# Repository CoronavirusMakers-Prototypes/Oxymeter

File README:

Repositorio del proyecto Oxymeter de Coronavirus Makers

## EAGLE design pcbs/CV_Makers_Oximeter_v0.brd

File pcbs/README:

Fuentes de las PCBs, BOMs, etc.

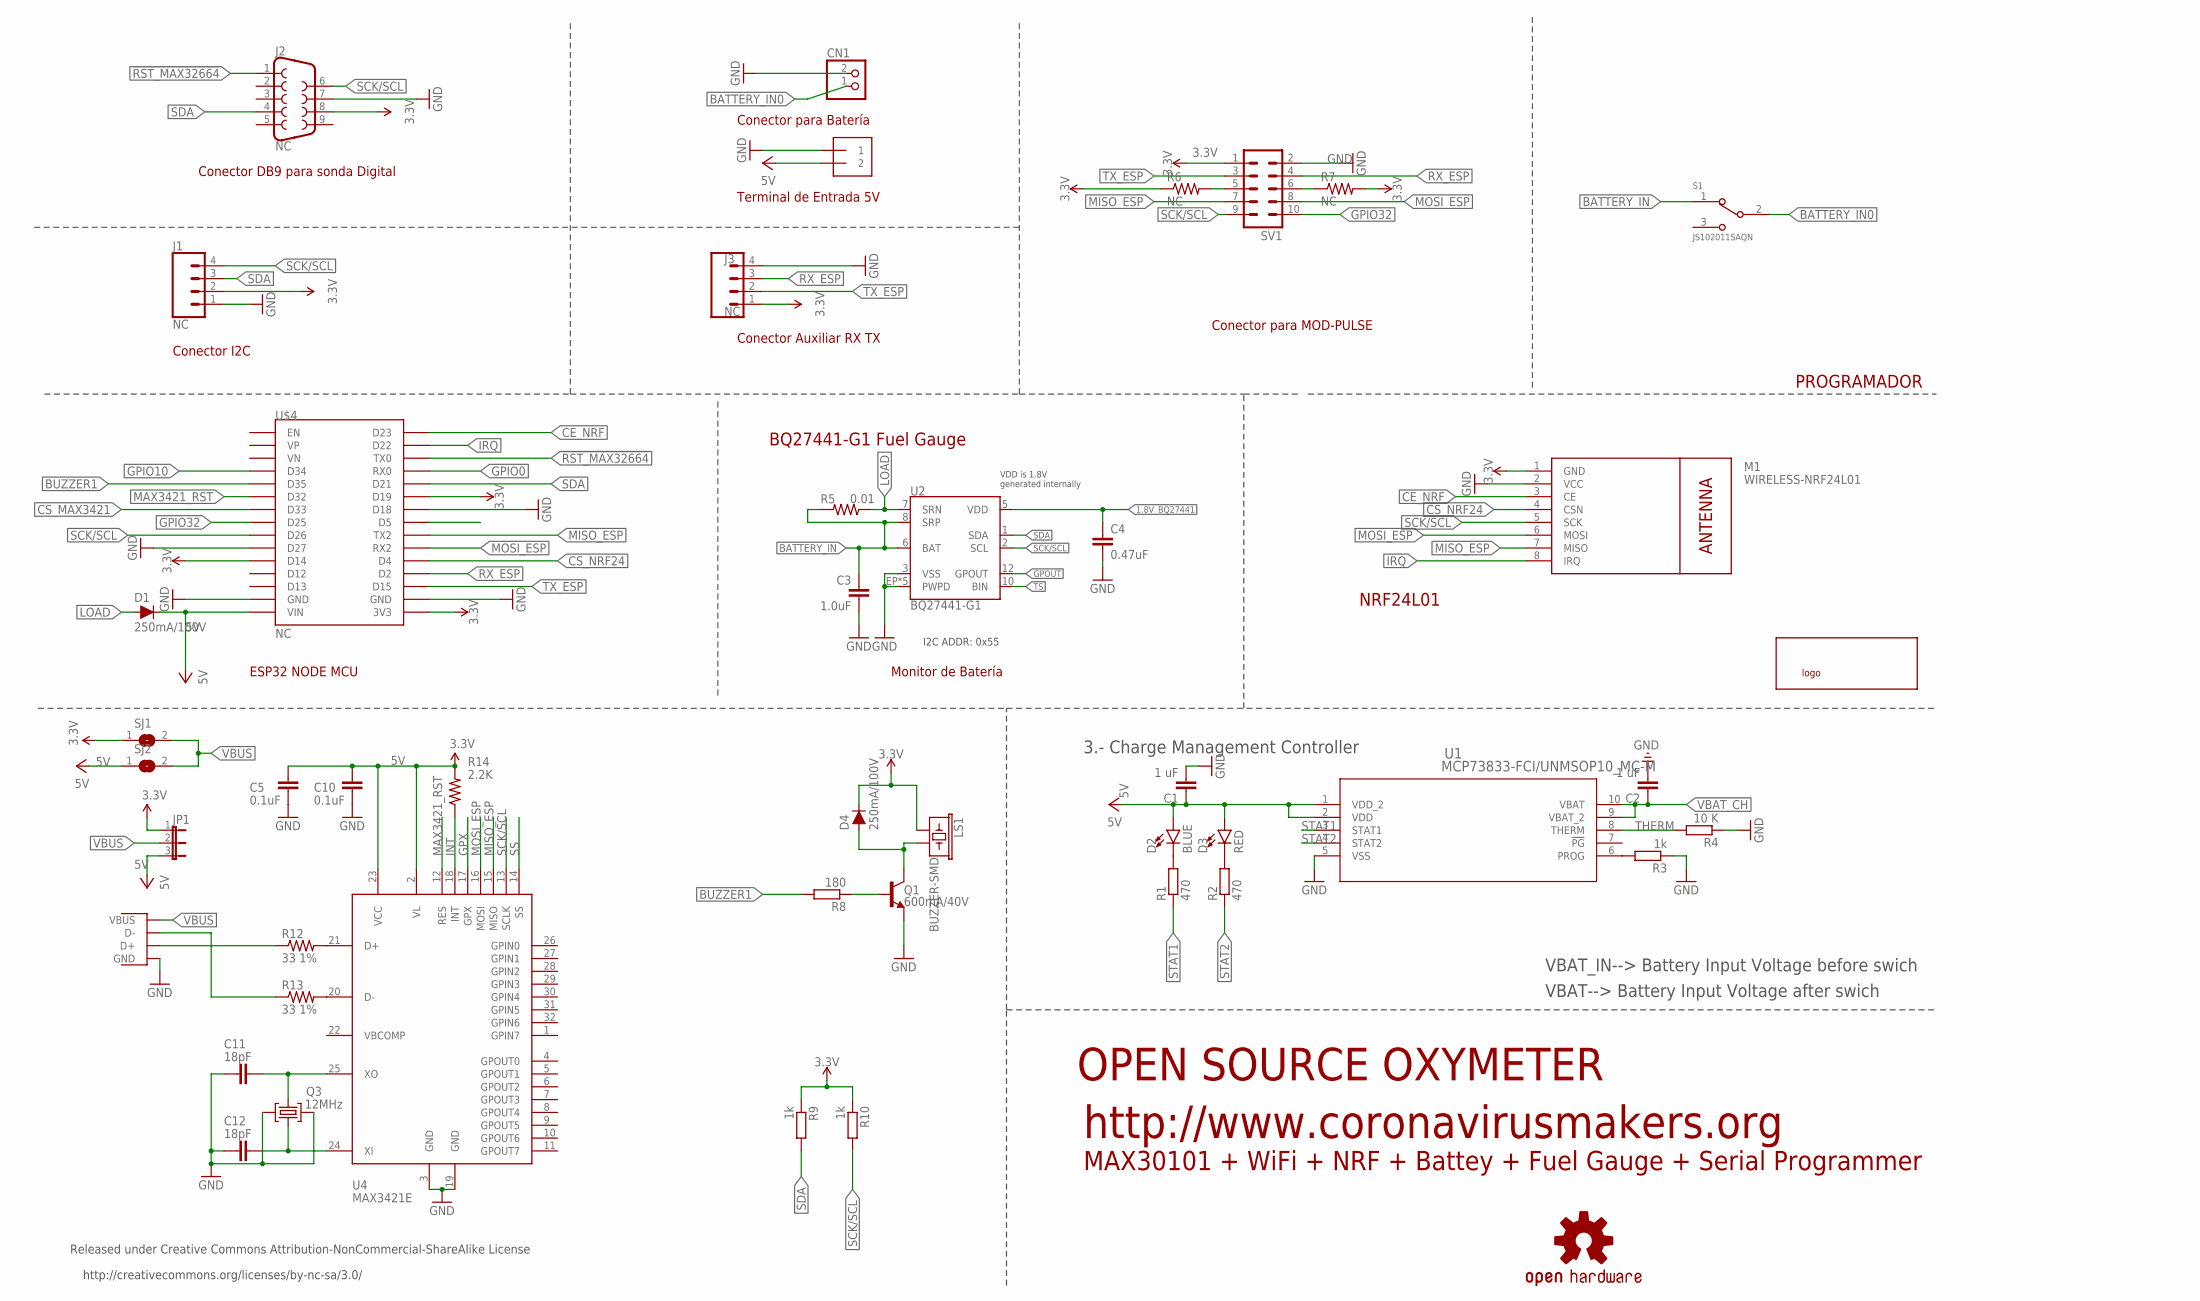
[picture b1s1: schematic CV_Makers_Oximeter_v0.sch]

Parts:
C1, C2: 1 uF; C0603
C3: 1.0uF; 0603-CAP
C4: 0.47uF; 0603-CAP
C5, C10: 0.1uF; 0603
C11, C12: 18pF; 0603
CN1: JST_2PIN-THM-RA; JST-PH-2-THM-RA
D1, D4: 250mA/100V; SOD-323
D2: BLUE; LED-0603
D3: RED; LED-0603
J1, J3: NC; 1X04
J2: NC; DB9
J4: NC; 1X2-3.5MM
JP1: JP2E; JP2
LOGO1: OSHW-LOGOL-COPPER; OSHW-LOGO-L_COPPER
LS1: BUZZER-SMD; BUZZER-CCV
M1: WIRELESS-NRF24L01
Q1: 600mA/40V; SOT23-3
Q3: 12MHz; CRYSTAL-SMD-5X3
R1, R2: 470; R0603
R3, R9, R10: 1k; R0603
R4: 10 K; R0603
R5: 0.01; 1206
R6, R7: NC; R0603
R8: 180; R0603
R12, R13: 33 1%; 0603
R14: 2.2K; 0603
S1: JS102011SAQN; SW_JS102011SAQN
SJ1, SJ2: SJ
SV1: ML10
U1: MCP73833-FCI/UNMSOP10_MC-M; MSOP10_MC-M
U2: BQ27441-G1; PDSO-N12
U4: MAX3421E; TQFP32_8MIL
U$2: LOGOEU; LOGO2
U$4: NC; ESP32_DEVKIT
X2: USB-A-H

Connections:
1.8V_BQ27441: C4.1, U2.5 (VDD)
3.3V: D4.C, J1.2, J2.8, J3.1, JP1.1, LS1.+ (1), M1.1 (GND), R6.1, R7.2, R9.1, R10.1, SJ1.1, SV1.1, U$4.D14, U$4.D19
5V: C1.1, C5.1, C10.1, D1.C, D2.A, D3.A, J4.2, JP1.3, R14.2, SJ2.1, U1.1 (VDD_2), U1.2 (VDD), U4.2 (VL), U4.23 (VCC), U$4.VIN
!RST_MAX32664: J2.1, U$4.TX0
BATTERY_IN: C3.1, R5.2, S1.1, U2.6 (BAT), U2.8 (SRP)
BATTERY_IN0: CN1.1 (2), S1.2
BUZZER1: R8.2, U$4.D35
CE_NRF: M1.3 (CE), U$4.D23
CS_MAX3421: U$4.D33
CS_NRF24: M1.4 (CSN), U$4.D4
GND: C1.2, C2.2, C3.2, C4.2, C5.2, C10.2, C11.1, C12.1, CN1.2 (1), J1.1, J2.7, J3.4, J4.1, M1.2 (VCC), Q1.2 (E), Q3.2 (3), Q3.4, R3.1, R4.1, SV1.2, U1.5 (VSS), U2.3 (VSS), U2.EP (PWPD), U2.EP1 (PWPD), U2.EP2 (PWPD), U2.EP3 (PWPD), U2.EP4 (PWPD), U4.3 (GND), U4.19 (GND), U$4.D18, U$4.GND@1 (GND), X2.GND
GPIO0: U$4.RX0
GPIO10: U$4.D34
GPIO32: SV1.10, U$4.D25
GPOUT: U2.12 (GPOUT)
GPX: U4.17 (GPX)
INT: R14.1, U4.18 (INT)
IRQ: M1.8 (IRQ), U$4.D22
LOAD: D1.A, R5.1, U2.7 (SRN)
MAX3421_RST: U4.12 (RES), U$4.D32
MISO_ESP: M1.7 (MISO), SV1.7, U4.15 (MISO), U$4.TX2
MOSI_ESP: M1.6 (MOSI), SV1.8, U4.16 (MOSI), U$4.RX2
unnamed: R6.2, SV1.5
unnamed: R7.1, SV1.6
unnamed: Q1.1 (B), R8.1
unnamed: D4.A, LS1.- (2), Q1.3 (C)
unnamed: R12.2, U4.21 (D+)
unnamed: D3.C, R2.2
unnamed: R13.2, U4.20 (D-)
unnamed: D2.C, R1.2
unnamed: R3.2, U1.6 (PROG)
unnamed: C11.2, Q3.3 (2), U4.25 (XO)
unnamed: C12.2, Q3.1, U4.24 (XI)
unnamed: R12.1, X2.D+
unnamed: R13.1, X2.D-
RX_ESP: J3.3, SV1.4, U$4.D2
SCK/SCL: J1.4, J2.6, M1.5 (SCK), R10.2, SV1.9, U2.2 (SCL), U4.13 (SCLK), U$4.D26
SDA: J1.3, J2.4, R9.2, U2.1 (SDA), U$4.D21
SS: U4.14 (SS)
STAT1: R1.1, U1.3 (STAT1)
STAT2: R2.1, U1.4 (STAT2)
THERM: R4.2, U1.8 (THERM)
TS: U2.10 (BIN)
TX_ESP: J3.2, SV1.3, U$4.D15
VBAT_CH: C2.1, U1.9 (VBAT_2), U1.10 (VBAT)
VBUS: JP1.2, SJ1.2, SJ2.2, X2.VBUS

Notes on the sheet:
BQ27441-G1 Fuel Gauge
VDD is 1.8V generated internally
I2C ADDR: 0x55
VBAT--> Battery Input Voltage after swich
VBAT_IN--> Battery Input Voltage before swich
3.- Charge Management Controller
PROGRAMADOR
http://www.coronavirusmakers.org
OPEN SOURCE OXYMETER
NRF24L01
MAX30101 + WiFi + NRF + Battey + Fuel Gauge + Serial Programmer
Conector DB9 para sonda Digital
Conector I2C
Conector Auxiliar RX TX
Conector para Batería
Terminal de Entrada 5V
ESP32 NODE MCU
Monitor de Batería
Conector para MOD-PULSE
Released under Creative Commons Attribution-NonCommercial-ShareAlike License
http://creativecommons.org/licenses/by-nc-sa/3.0/

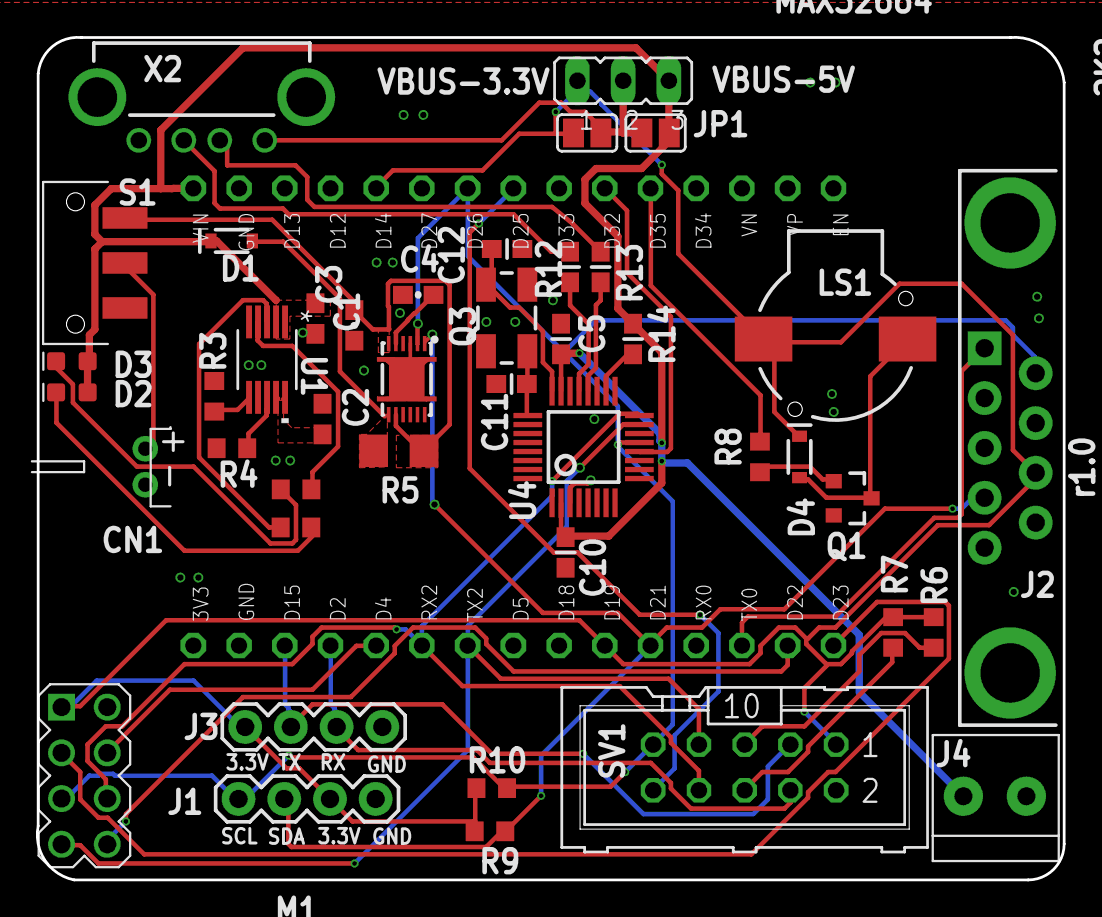
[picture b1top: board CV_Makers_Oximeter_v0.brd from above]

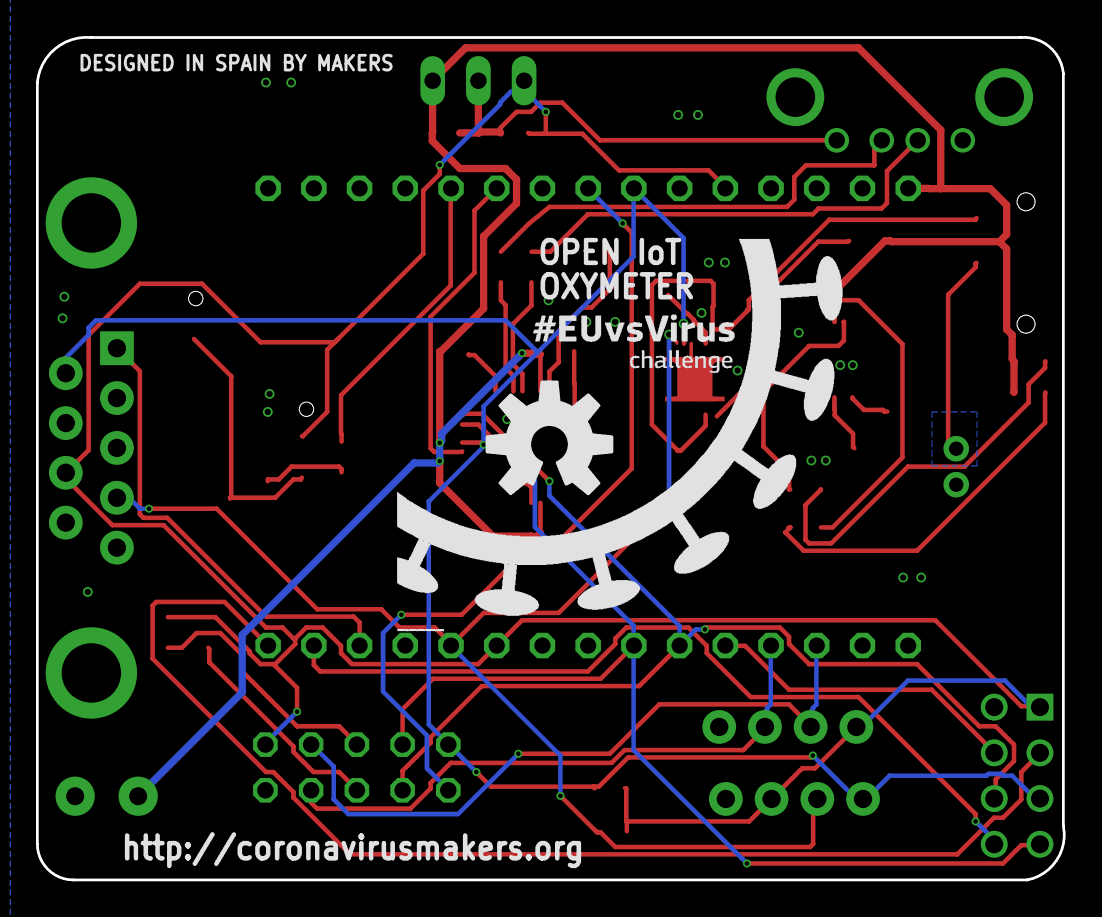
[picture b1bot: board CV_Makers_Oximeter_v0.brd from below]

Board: 2 copper layers, 57.0 x 46.8 mm, 47 parts (2 on the bottom side), 39 nets.

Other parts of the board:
U$1: OSHW-LOGO-L

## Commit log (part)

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2020-03-30 Carga inicial
2020-03-30 first commit, structure, db connections, config
2020-03-30 starting
2020-03-30 websockes rogue
2020-03-30 docker-compose for postgresql dependency
2020-03-31 database design
2020-03-31 adding database from master
2020-03-31 Arquitectura front
2020-04-01 trying to create tables on init via sql file
2020-04-01 Modified User table with jws field
2020-04-01 init database on start if that does not exists, refactoring folder names and adding gitignore to root of repo
2020-04-01 Login / formulario registro / authguard
2020-04-02 basic endpoint for meassurement and sensor, something at README
2020-04-02 first commit to develop
2020-04-02 readme
2020-04-02 simple logging
2020-04-02 removing logs
2020-04-03 better queries handling
2020-04-03 adding checks for request params, more or less ready for duplicate
2020-04-03 improving README
2020-04-03 Componentes por zona
2020-04-03 basic sender and consumer for rabbit, now lets start play around
2020-04-03 adding array payloads for dummy-senders and implementation at the consummer side
2020-04-03 RabbitMQ consumer implementation almost there
2020-04-03 adding rabbitmq for docker composition
2020-04-03 adding credentials to rabbitmq
2020-04-03 Estructura hospital / migas de pan / componente alarmas / servicio utils / servicio alarms / encapsular servicios en global.service
2020-04-04 adding all semicolons since ASI and its excentric behavior and async do things on startup
2020-04-04 changed response to get list for pagination
2020-04-04 updating insomnia export
2020-04-04 implementing rabbitmq sender
2020-04-04 Thanks co 🙏
2020-04-05 Logout a través de globalService / nuevo bed sensor patient service / quito user-asignement.service.ts / clear localStorage on logout
2020-04-05 adding area endpoint and changes at queries to match the new naming
2020-04-05 hospitals working
2020-04-05 build working
2020-04-05 floors working
2020-04-05 room working
2020-04-05 bed working and fix missing id at dummy senders
2020-04-05 roles working
2020-04-05 Servicio paciente
2020-04-05 patient working
2020-04-05 Database modifications
2020-04-05 Sensor data
2020-04-05 updating insomnia file
2020-04-06 new database
2020-04-06 lot of stuff
2020-04-06 Cambio nombre servicio
2020-04-06 Prueba librería gráficas
2020-04-06 Urls librería chart
2020-04-06 added TODOs and descriptions
2020-04-07 Modificación nombres endpoints
2020-04-07 complete and align new endpoints names
2020-04-08 Gráficas
2020-04-08 Modificación de endpoints
2020-04-08 Fallo en subscripción / mejorar tarjetas notificación
2020-04-08 Revert "Merge branch 'develop' of https://github.com/CoronavirusMakers-Prototypes/Oxymeter into develop"
    This reverts commit 1a4c3f17e7040101b00fa4e6424192259ffcb72c, reversing
    changes made to b62493db245b4d57c293fa6242d600d76920510d.
2020-04-08 Revert "Revert "Merge branch 'develop' of https://github.com/CoronavirusMakers-Prototypes/Oxymeter into develop""
    This reverts commit f828940f6e71ad461d962e2c8fefcd276c3060b3.
2020-04-08 Create LICENSE_SOFT.md
    Software License
2020-04-08 Recuperar front
2020-04-10 sketch
2020-04-10 Alarms sounds / alarms view /socket sevice
2020-04-10 implememting ws
2020-04-12 resolving a bubu on a PR...
2020-04-12 adding jwt to database on create user
2020-04-12 basic login
2020-04-12 tokens validator for requests, and some refactoring
2020-04-13 adding middleware to deal with jwt validations present at headres and excluding endpoints to POST data from probes
2020-04-13 logout added
2020-04-13 adding getById* area, bed, build, floor, room
2020-04-14 adding get patinent by id bed
2020-04-15 Optimized multithread non blocking alarm processing
    Base code. Has to be completed (multithread support), compiled and tested.
2020-04-15 Update meassurementController.js
    Remove comments
2020-04-15 Licence and alarms info
2020-04-16 removing hash in server side, adding GET hospitals and signin to not check jwt, role and last login not mandatory anymore to signin
2020-04-17 Endpoint sigin
2020-04-19 array is default to process data, query patients data optimized
2020-04-19 Create oxyFirmware
    Firmware 1.0 de la ESP32 para el proyecto basado en el italiano. No sé si compila, mucho menos si funciona.
2020-04-19 before node-cache
2020-04-20 Problemas gráficas
2020-04-20 cache for patient data implemented
2020-04-20 adding alarmInterval and ttl to config
2020-04-20 Botones para crear estructura hospital
2020-04-21 Servicios endpoint builds
2020-04-21 Alarms icons
2020-04-22 Created queries and endpoints (list alarms suscriptions by userid, last 100 meassurements by patient or bysensor, get active alarms for a userid)
2020-04-23 Versión estable
2020-04-24 Mock demos socket.service
2020-04-24 Mostrar alerta alarma a nivel habitación y área
2020-04-24 more things
2020-04-24 Versión Demo
2020-04-24 sending list of suscriptions on creating a suscription
2020-04-24 sending time of metric as timestam instead a date string
2020-04-24 fixing a boob identation
2020-04-24 English version
2020-04-25 not mandatory idRoom for POST suscriptions
2020-04-25 solving alarm active by user id
2020-04-25 adding description for alarms bed, area, room
2020-04-26 fixing typo
2020-04-26 experimenting with errors
2020-04-26 better herror handling
2020-04-26 Notifications / Bed component
2020-04-26 Uploaded Board files
2020-04-28 updating query activeByUserId
2020-04-28 custom error answer for jwt
2020-05-02 console socket
2020-05-02 Formulario alta paciente
2020-05-03 PUT patient not mandatory status, suscribed and unsuscribed
2020-05-03 adding endpoing /beds/available to return all beds that are not been used. also refactoring test_meassurement.sh to better spot
2020-05-03 new line removed
2020-05-03 Cambios pantalla cama
2020-07-20 Bump lodash from 4.17.15 to 4.17.19 in /src/backend
    Bumps [lodash](https://github.com/lodash/lodash) from 4.17.15 to 4.17.19.
    - [Release notes](https://github.com/lodash/lodash/releases)
    - [Commits](https://github.com/lodash/lodash/compare/4.17.15...4.17.19)
2020-12-12 Bump ini from 1.3.5 to 1.3.8 in /src/backend
    Bumps [ini](https://github.com/isaacs/ini) from 1.3.5 to 1.3.8.
    - [Release notes](https://github.com/isaacs/ini/releases)
    - [Commits](https://github.com/isaacs/ini/compare/v1.3.5...v1.3.8)
2021-01-21 Bump socket.io from 2.3.0 to 2.4.0 in /src/backend
    Bumps [socket.io](https://github.com/socketio/socket.io) from 2.3.0 to 2.4.0.
    - [Release notes](https://github.com/socketio/socket.io/releases)
    - [Changelog](https://github.com/socketio/socket.io/blob/2.4.0/CHANGELOG.md)
    - [Commits](https://github.com/socketio/socket.io/compare/2.3.0...2.4.0)
2021-03-31 Bump y18n from 3.2.1 to 3.2.2 in /src/backend
    Bumps [y18n](https://github.com/yargs/y18n) from 3.2.1 to 3.2.2.
    - [Release notes](https://github.com/yargs/y18n/releases)
    - [Changelog](https://github.com/yargs/y18n/blob/master/CHANGELOG.md)
    - [Commits](https://github.com/yargs/y18n/commits)
2021-05-11 Bump lodash from 4.17.15 to 4.17.21 in /src/backend
    Bumps [lodash](https://github.com/lodash/lodash) from 4.17.15 to 4.17.21.
    - [Release notes](https://github.com/lodash/lodash/releases)
    - [Commits](https://github.com/lodash/lodash/compare/4.17.15...4.17.21)
2021-06-11 Bump glob-parent from 5.1.1 to 5.1.2 in /src/backend
    Bumps [glob-parent](https://github.com/gulpjs/glob-parent) from 5.1.1 to 5.1.2.
    - [Release notes](https://github.com/gulpjs/glob-parent/releases)
    - [Changelog](https://github.com/gulpjs/glob-parent/blob/main/CHANGELOG.md)
    - [Commits](https://github.com/gulpjs/glob-parent/compare/v5.1.1...v5.1.2)
    ---
    updated-dependencies:
2021-06-30 Bump socket.io-parser from 3.3.0 to 3.3.2 in /src/backend
    Bumps [socket.io-parser](https://github.com/socketio/socket.io-parser) from 3.3.0 to 3.3.2.
    - [Release notes](https://github.com/socketio/socket.io-parser/releases)
    - [Changelog](https://github.com/socketio/socket.io-parser/blob/3.3.2/CHANGELOG.md)
    - [Commits](https://github.com/socketio/socket.io-parser/compare/3.3.0...3.3.2)
    ---
    updated-dependencies:
2021-08-12 Bump path-parse from 1.0.6 to 1.0.7 in /src/backend
    Bumps [path-parse](https://github.com/jbgutierrez/path-parse) from 1.0.6 to 1.0.7.
    - [Release notes](https://github.com/jbgutierrez/path-parse/releases)
    - [Commits](https://github.com/jbgutierrez/path-parse/commits/v1.0.7)
    ---
    updated-dependencies:
    - dependency-name: path-parse
2022-02-11 Bump karma from 4.4.1 to 6.3.14 in /src/frontend
    Bumps [karma](https://github.com/karma-runner/karma) from 4.4.1 to 6.3.14.
    - [Release notes](https://github.com/karma-runner/karma/releases)
    - [Changelog](https://github.com/karma-runner/karma/blob/master/CHANGELOG.md)
    - [Commits](https://github.com/karma-runner/karma/compare/v4.4.1...v6.3.14)
    ---
    updated-dependencies:
2022-03-02 Bump karma from 4.4.1 to 6.3.16 in /src/frontend
    Bumps [karma](https://github.com/karma-runner/karma) from 4.4.1 to 6.3.16.
    - [Release notes](https://github.com/karma-runner/karma/releases)
    - [Changelog](https://github.com/karma-runner/karma/blob/master/CHANGELOG.md)
    - [Commits](https://github.com/karma-runner/karma/compare/v4.4.1...v6.3.16)
    ---
    updated-dependencies:
2022-04-09 Bump moment from 2.24.0 to 2.29.2 in /src/backend
    Bumps [moment](https://github.com/moment/moment) from 2.24.0 to 2.29.2.
    - [Release notes](https://github.com/moment/moment/releases)
    - [Changelog](https://github.com/moment/moment/blob/develop/CHANGELOG.md)
    - [Commits](https://github.com/moment/moment/compare/2.24.0...2.29.2)
    ---
    updated-dependencies:
2022-04-29 Bump async from 2.6.3 to 2.6.4 in /src/backend
    Bumps [async](https://github.com/caolan/async) from 2.6.3 to 2.6.4.
    - [Release notes](https://github.com/caolan/async/releases)
    - [Changelog](https://github.com/caolan/async/blob/v2.6.4/CHANGELOG.md)
    - [Commits](https://github.com/caolan/async/compare/v2.6.3...v2.6.4)
    ---
    updated-dependencies:
2022-06-03 Bump @angular/core from 9.1.0 to 11.0.5 in /src/frontend
    Bumps [@angular/core](https://github.com/angular/angular/tree/HEAD/packages/core) from 9.1.0 to 11.0.5.
    - [Release notes](https://github.com/angular/angular/releases)
    - [Changelog](https://github.com/angular/angular/blob/main/CHANGELOG.md)
    - [Commits](https://github.com/angular/angular/commits/11.0.5/packages/core)
    ---
    updated-dependencies:
2022-07-07 Bump moment from 2.24.0 to 2.29.4 in /src/backend
    Bumps [moment](https://github.com/moment/moment) from 2.24.0 to 2.29.4.
    - [Release notes](https://github.com/moment/moment/releases)
    - [Changelog](https://github.com/moment/moment/blob/develop/CHANGELOG.md)
    - [Commits](https://github.com/moment/moment/compare/2.24.0...2.29.4)
    ---
    updated-dependencies:
2022-11-09 Bump socket.io-parser from 3.3.0 to 3.3.3 in /src/backend
    Bumps [socket.io-parser](https://github.com/socketio/socket.io-parser) from 3.3.0 to 3.3.3.
    - [Release notes](https://github.com/socketio/socket.io-parser/releases)
    - [Changelog](https://github.com/socketio/socket.io-parser/blob/main/CHANGELOG.md)
    - [Commits](https://github.com/socketio/socket.io-parser/compare/3.3.0...3.3.3)
    ---
    updated-dependencies:
2022-12-22 Bump jsonwebtoken from 8.5.1 to 9.0.0 in /src/backend
    Bumps [jsonwebtoken](https://github.com/auth0/node-jsonwebtoken) from 8.5.1 to 9.0.0.
    - [Release notes](https://github.com/auth0/node-jsonwebtoken/releases)
    - [Changelog](https://github.com/auth0/node-jsonwebtoken/blob/master/CHANGELOG.md)
    - [Commits](https://github.com/auth0/node-jsonwebtoken/compare/v8.5.1...v9.0.0)
    ---
    updated-dependencies:

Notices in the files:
parts and their libraries:
SparkFun-Resistors: Licensing: Creative Commons ShareAlike 4.0 International - https://creativecommons.org/licenses/by-sa/4.0
diy-modules: Released under the Creative Commons Attribution 4.0 International License: http://creativecommons.org/licenses/by/4.0
supply1: Copyright (C) 2007, Bob Starr
